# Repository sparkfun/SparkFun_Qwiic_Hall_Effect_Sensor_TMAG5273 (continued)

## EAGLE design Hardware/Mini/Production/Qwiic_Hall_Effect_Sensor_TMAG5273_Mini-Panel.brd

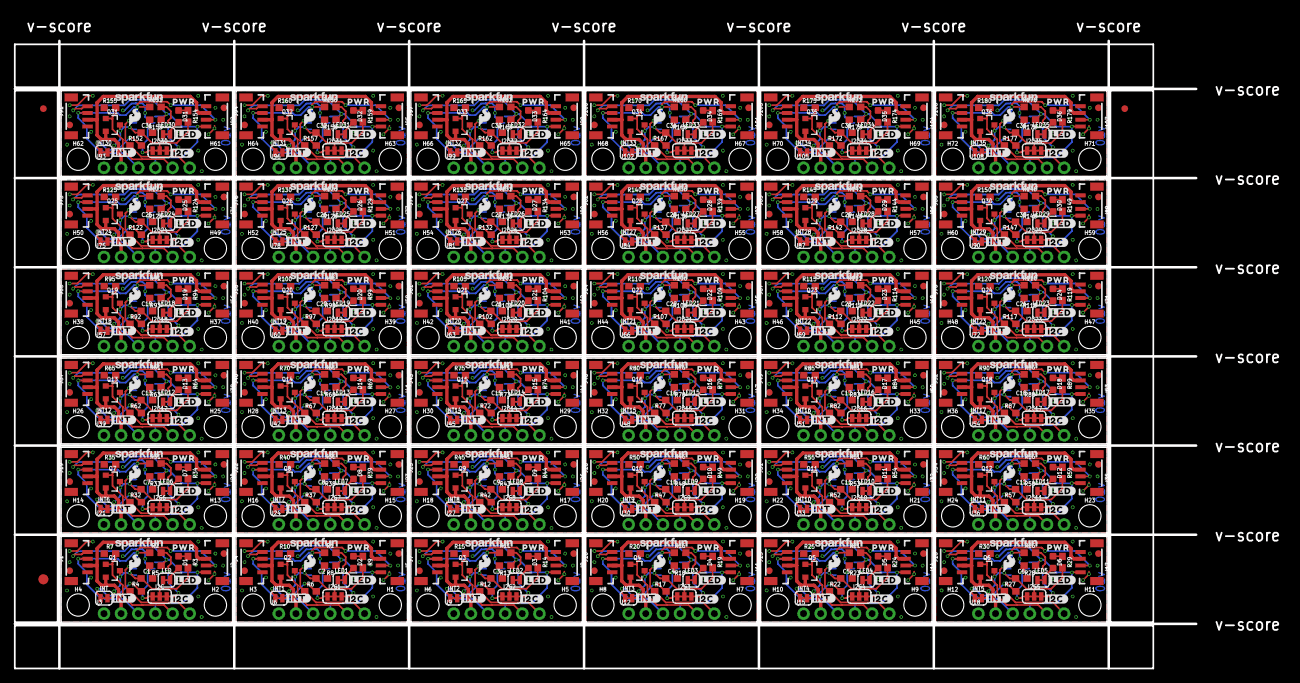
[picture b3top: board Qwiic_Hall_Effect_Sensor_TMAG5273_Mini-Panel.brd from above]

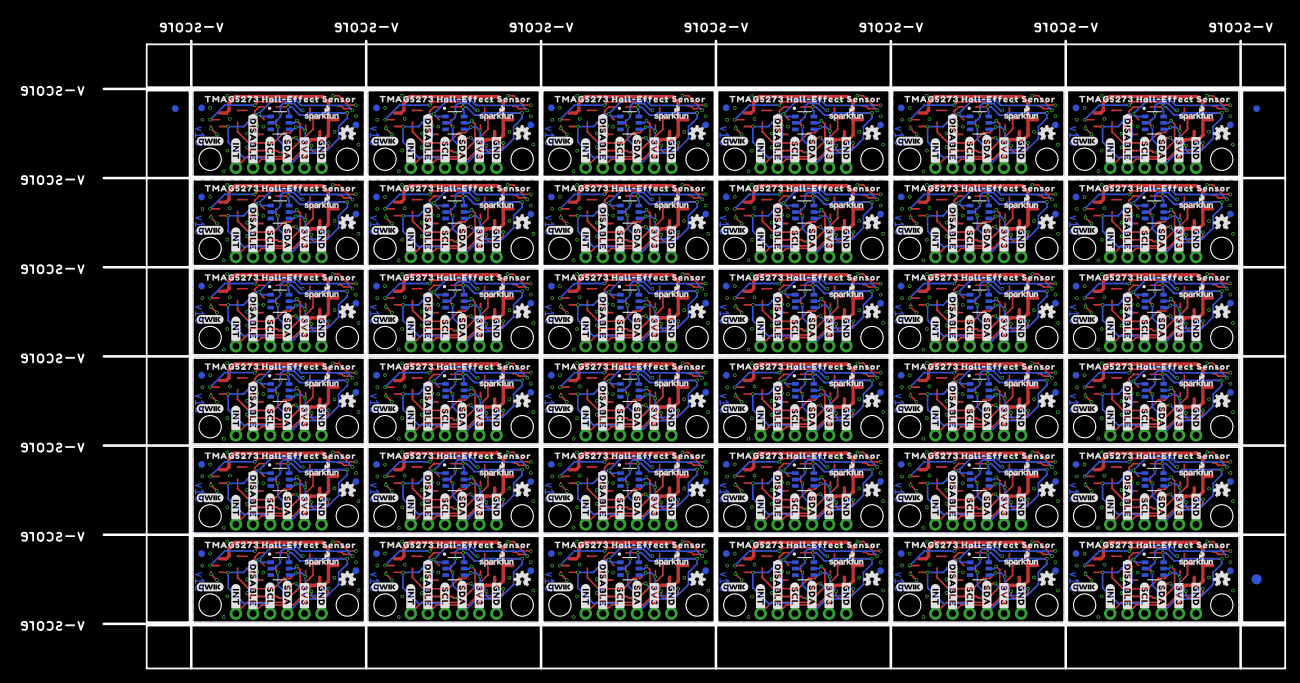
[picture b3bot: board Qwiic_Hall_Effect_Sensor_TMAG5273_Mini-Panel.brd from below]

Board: 2 copper layers, 188.2 x 96.8 mm, 1338 parts (471 on the bottom side), 432 nets.

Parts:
C1, C2, C3, C4, C5, C6, C7, C8, C9, C10, C11, C12, C13, C14, C15, C16, C17, C18, C19, C20, C21, C22, C23, C24, C25, C26, C27, C28, C29, C30, C31, C32, C33, C34, C35, C36: 0.1uF; 0603
D1, D2, D3, D4, D5, D6, D7, D8, D9, D10, D11, D12, D13, D14, D15, D16, D17, D18, D19, D20, D21, D22, D23, D24, D25, D26, D27, D28, D29, D30, D31, D32, D33, D34, D35, D36: Red; LED-0603
E$1, E$2, E$3, E$4: FIDUCIAL-1X2
E$5, E$6: FIDUCIAL-1.5X3
FD1, FD2, FD3, FD4, FD5, FD6, FD7, FD8, FD9, FD10, FD11, FD12, FD13, FD14, FD15, FD16, FD17, FD18, FD19, FD20, FD21, FD22, FD23, FD24, FD25, FD26, FD27, FD28, FD29, FD30, FD31, FD32, FD33, FD34, FD35, FD36, FD37, FD38, FD39, FD40, FD41, FD42, FD43, FD44, FD45, FD46, FD47, FD48, FD49, FD50, FD51, FD52, FD53, FD54, FD55, FD56, FD57, FD58, FD59, FD60, FD61, FD62, FD63, FD64, FD65, FD66, FD67, FD68, FD69, FD70, FD71, FD72, FD73, FD74, FD75, FD76, FD77, FD78, FD79, FD80, FD81, FD82, FD83, FD84, FD85, FD86, FD87, FD88, FD89, FD90, FD91, FD92, FD93, FD94, FD95, FD96, FD97, FD98, FD99, FD100, FD101, FD102, FD103, FD104, FD105, FD106, FD107, FD108, FD109, FD110, FD111, FD112, FD113, FD114, FD115, FD116, FD117, FD118, FD119, FD120, FD121, FD122, FD123, FD124, FD125, FD126, FD127, FD128, FD129, FD130, FD131, FD132, FD133, FD134, FD135, FD136, FD137, FD138, FD139, FD140, FD141, FD142, FD143, FD144: FIDUCIAL1X2; FIDUCIAL-1X2
H1, H2, H3, H4, H5, H6, H7, H8, H9, H10, H11, H12, H13, H14, H15, H16, H17, H18, H19, H20, H21, H22, H23, H24, H25, H26, H27, H28, H29, H30, H31, H32, H33, H34, H35, H36, H37, H38, H39, H40, H41, H42, H43, H44, H45, H46, H47, H48, H49, H50, H51, H52, H53, H54, H55, H56, H57, H58, H59, H60, H61, H62, H63, H64, H65, H66, H67, H68, H69, H70, H71, H72: STAND-OFF
I2C, I2C1, I2C2, I2C3, I2C4, I2C5, I2C6, I2C7, I2C8, I2C9, I2C10, I2C11, I2C12, I2C13, I2C14, I2C15, I2C16, I2C17, I2C18, I2C19, I2C20, I2C21, I2C22, I2C23, I2C24, I2C25, I2C26, I2C27, I2C28, I2C29, I2C30, I2C31, I2C32, I2C33, I2C34, I2C35: JUMPER-SMT_3_2-NC_TRACE_SILK; SMT-JUMPER_3_2-NC_TRACE_SILK
INT, INT1, INT2, INT3, INT4, INT5, INT6, INT7, INT8, INT9, INT10, INT11, INT12, INT13, INT14, INT15, INT16, INT17, INT18, INT19, INT20, INT21, INT22, INT23, INT24, INT25, INT26, INT27, INT28, INT29, INT30, INT31, INT32, INT33, INT34, INT35: JUMPER-SMT_2_NC_TRACE_SILK; SMT-JUMPER_2_NC_TRACE_SILK
J1, J2, J4, J5, J7, J8, J10, J11, J13, J14, J16, J17, J19, J20, J22, J23, J25, J26, J28, J29, J31, J32, J34, J35, J37, J38, J40, J41, J43, J44, J46, J47, J49, J50, J52, J53, J55, J56, J58, J59, J61, J62, J64, J65, J67, J68, J70, J71, J73, J74, J76, J77, J79, J80, J82, J83, J85, J86, J88, J89, J91, J92, J94, J95, J97, J98, J100, J101, J103, J104, J106, J107: Vertical Qwiic Connector; JST04_1MM_VERT
J3, J6, J9, J12, J15, J18, J21, J24, J27, J30, J33, J36, J39, J42, J45, J48, J51, J54, J57, J60, J63, J66, J69, J72, J75, J78, J81, J84, J87, J90, J93, J96, J99, J102, J105, J108: 1X06_NO_SILK
LED, LED1, LED2, LED3, LED4, LED5, LED6, LED7, LED8, LED9, LED10, LED11, LED12, LED13, LED14, LED15, LED16, LED17, LED18, LED19, LED20, LED21, LED22, LED23, LED24, LED25, LED26, LED27, LED28, LED29, LED30, LED31, LED32, LED33, LED34, LED35: JUMPER-SMT_2_NC_TRACE_SILK; SMT-JUMPER_2_NC_TRACE_SILK
LOGO1, LOGO5, LOGO11, LOGO16, LOGO21, LOGO26, LOGO31, LOGO36, LOGO41, LOGO46, LOGO51, LOGO56, LOGO61, LOGO66, LOGO71, LOGO76, LOGO81, LOGO86, LOGO91, LOGO96, LOGO101, LOGO106, LOGO111, LOGO116, LOGO121, LOGO126, LOGO131, LOGO136, LOGO141, LOGO146, LOGO151, LOGO156, LOGO161, LOGO166, LOGO171, LOGO176: OSHW-LOGOMINI; OSHW-LOGO-MINI
LOGO2, LOGO7, LOGO12, LOGO17, LOGO22, LOGO27, LOGO32, LOGO37, LOGO42, LOGO47, LOGO52, LOGO57, LOGO62, LOGO67, LOGO72, LOGO77, LOGO82, LOGO87, LOGO92, LOGO97, LOGO102, LOGO107, LOGO112, LOGO117, LOGO122, LOGO127, LOGO132, LOGO137, LOGO142, LOGO147, LOGO152, LOGO157, LOGO162, LOGO167, LOGO172, LOGO177: SFE_LOGO_NAME_FLAME5_MM; SFE_LOGO_NAME_FLAME_5MM
LOGO3, LOGO8, LOGO13, LOGO18, LOGO23, LOGO28, LOGO33, LOGO38, LOGO43, LOGO48, LOGO53, LOGO58, LOGO63, LOGO68, LOGO73, LOGO78, LOGO83, LOGO88, LOGO93, LOGO98, LOGO103, LOGO108, LOGO113, LOGO118, LOGO123, LOGO128, LOGO133, LOGO138, LOGO143, LOGO148, LOGO153, LOGO158, LOGO163, LOGO168, LOGO173, LOGO178: QWIIC_LOGO_4MM; QWIIC_4MM
LOGO4, LOGO9, LOGO14, LOGO19, LOGO24, LOGO29, LOGO34, LOGO39, LOGO44, LOGO49, LOGO54, LOGO59, LOGO64, LOGO69, LOGO74, LOGO79, LOGO84, LOGO89, LOGO94, LOGO99, LOGO104, LOGO109, LOGO114, LOGO119, LOGO124, LOGO129, LOGO134, LOGO139, LOGO144, LOGO149, LOGO154, LOGO159, LOGO164, LOGO169, LOGO174, LOGO179: SFE_LOGO_NAME7_MM; SFE_LOGO_NAME_7MM
LOGO6, LOGO10, LOGO15, LOGO20, LOGO25, LOGO30, LOGO35, LOGO40, LOGO45, LOGO50, LOGO55, LOGO60, LOGO65, LOGO70, LOGO75, LOGO80, LOGO85, LOGO90, LOGO95, LOGO100, LOGO105, LOGO110, LOGO115, LOGO120, LOGO125, LOGO130, LOGO135, LOGO140, LOGO145, LOGO150, LOGO155, LOGO160, LOGO165, LOGO170, LOGO175, LOGO180: SFE_LOGO_FLAME.1_INCH; SFE_LOGO_FLAME_.1
Q1, Q2, Q3, Q4, Q5, Q6, Q7, Q8, Q9, Q10, Q11, Q12, Q13, Q14, Q15, Q16, Q17, Q18, Q19, Q20, Q21, Q22, Q23, Q24, Q25, Q26, Q27, Q28, Q29, Q30, Q31, Q32, Q33, Q34, Q35, Q36: 20V/4.2A/52mΩ/1.4W; SOT23-3
R1, R2, R5, R8, R11, R13, R16, R18, R21, R23, R26, R28, R31, R33, R36, R38, R41, R43, R46, R48, R51, R53, R56, R58, R61, R63, R66, R68, R71, R73, R76, R78, R81, R83, R86, R88, R91, R93, R96, R98, R101, R103, R106, R108, R111, R113, R116, R118, R121, R123, R126, R128, R131, R133, R136, R138, R141, R143, R146, R148, R151, R153, R156, R158, R161, R163, R166, R168, R171, R173, R176, R178: 2.2k; 0603
R3, R9, R14, R19, R24, R29, R34, R39, R44, R49, R54, R59, R64, R69, R74, R79, R84, R89, R94, R99, R104, R109, R114, R119, R124, R129, R134, R139, R144, R149, R154, R159, R164, R169, R174, R179: 4.7k; 0603
R4, R6, R7, R10, R12, R15, R17, R20, R22, R25, R27, R30, R32, R35, R37, R40, R42, R45, R47, R50, R52, R55, R57, R60, R62, R65, R67, R70, R72, R75, R77, R80, R82, R85, R87, R90, R92, R95, R97, R100, R102, R105, R107, R110, R112, R115, R117, R120, R122, R125, R127, R130, R132, R135, R137, R140, R142, R145, R147, R150, R152, R155, R157, R160, R162, R165, R167, R170, R172, R175, R177, R180: 10k; 0603
U1, U2, U3, U4, U5, U6, U7, U8, U9, U10, U11, U12, U13, U14, U15, U16, U17, U18, U19, U20, U21, U22, U23, U24, U25, U26, U27, U28, U29, U30, U31, U32, U33, U34, U35, U36: TMAG5273; SOT23-6_DBV_TEX
U$1, U$19, U$30, U$41, U$52, U$63, U$74, U$85, U$96, U$107, U$118, U$129, U$140, U$151, U$162, U$173, U$184, U$195, U$206, U$217, U$228, U$239, U$250, U$261, U$272, U$283, U$294, U$305, U$316, U$327, U$338, U$349, U$360, U$371, U$382, U$393: PWR5282
U$2, U$11, U$23, U$34, U$45, U$56, U$67, U$78, U$89, U$100, U$111, U$122, U$133, U$144, U$155, U$166, U$177, U$188, U$199, U$210, U$221, U$232, U$243, U$254, U$265, U$276, U$287, U$298, U$309, U$320, U$331, U$342, U$353, U$364, U$375, U$386: #SCL#38
U$3, U$13, U$24, U$35, U$46, U$57, U$68, U$79, U$90, U$101, U$112, U$123, U$134, U$145, U$156, U$167, U$178, U$189, U$200, U$211, U$222, U$233, U$244, U$255, U$266, U$277, U$288, U$299, U$310, U$321, U$332, U$343, U$354, U$365, U$376, U$387: #SDA#37
U$4, U$14, U$25, U$36, U$47, U$58, U$69, U$80, U$91, U$102, U$113, U$124, U$135, U$146, U$157, U$168, U$179, U$190, U$201, U$212, U$223, U$234, U$245, U$256, U$267, U$278, U$289, U$300, U$311, U$322, U$333, U$344, U$355, U$366, U$377, U$388: #3V3#37
U$5, U$15, U$26, U$37, U$48, U$59, U$70, U$81, U$92, U$103, U$114, U$125, U$136, U$147, U$158, U$169, U$180, U$191, U$202, U$213, U$224, U$235, U$246, U$257, U$268, U$279, U$290, U$301, U$312, U$323, U$334, U$345, U$356, U$367, U$378, U$389: #GND#36
U$6, U$16, U$27, U$38, U$49, U$60, U$71, U$82, U$93, U$104, U$115, U$126, U$137, U$148, U$159, U$170, U$181, U$192, U$203, U$214, U$225, U$236, U$247, U$258, U$269, U$280, U$291, U$302, U$313, U$324, U$335, U$346, U$357, U$368, U$379, U$390: TMAG5273_HALL#EFFECT_SENSOR0
U$7, U$22, U$33, U$44, U$55, U$66, U$77, U$88, U$99, U$110, U$121, U$132, U$143, U$154, U$165, U$176, U$187, U$198, U$209, U$220, U$231, U$242, U$253, U$264, U$275, U$286, U$297, U$308, U$319, U$330, U$341, U$352, U$363, U$374, U$385, U$396: #DISABLE#5291
U$8, U$17, U$28, U$39, U$50, U$61, U$72, U$83, U$94, U$105, U$116, U$127, U$138, U$149, U$160, U$171, U$182, U$193, U$204, U$215, U$226, U$237, U$248, U$259, U$270, U$281, U$292, U$303, U$314, U$325, U$336, U$347, U$358, U$369, U$380, U$391: #I2C#5276
U$9, U$20, U$31, U$42, U$53, U$64, U$75, U$86, U$97, U$108, U$119, U$130, U$141, U$152, U$163, U$174, U$185, U$196, U$207, U$218, U$229, U$240, U$251, U$262, U$273, U$284, U$295, U$306, U$317, U$328, U$339, U$350, U$361, U$372, U$383, U$394: #INT#5285
U$10, U$18, U$29, U$40, U$51, U$62, U$73, U$84, U$95, U$106, U$117, U$128, U$139, U$150, U$161, U$172, U$183, U$194, U$205, U$216, U$227, U$238, U$249, U$260, U$271, U$282, U$293, U$304, U$315, U$326, U$337, U$348, U$359, U$370, U$381, U$392: #LED#5275
U$12, U$21, U$32, U$43, U$54, U$65, U$76, U$87, U$98, U$109, U$120, U$131, U$142, U$153, U$164, U$175, U$186, U$197, U$208, U$219, U$230, U$241, U$252, U$263, U$274, U$285, U$296, U$307, U$318, U$329, U$340, U$351, U$362, U$373, U$384, U$395: #INT#5287

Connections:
3.3V: J1.2, J2.2, J3.2, Q1.2
3.3V1: J4.2, J5.2, J6.2, Q2.2
3.3V2: J7.2, J8.2, J9.2, Q3.2
3.3V3: J10.2, J11.2, J12.2, Q4.2
3.3V4: J13.2, J14.2, J15.2, Q5.2
3.3V5: J16.2, J17.2, J18.2, Q6.2
3.3V6: J19.2, J20.2, J21.2, Q7.2
3.3V7: J22.2, J23.2, J24.2, Q8.2
3.3V8: J25.2, J26.2, J27.2, Q9.2
3.3V9: J28.2, J29.2, J30.2, Q10.2
3.3V10: J31.2, J32.2, J33.2, Q11.2
3.3V11: J34.2, J35.2, J36.2, Q12.2
3.3V12: J37.2, J38.2, J39.2, Q13.2
3.3V13: J40.2, J41.2, J42.2, Q14.2
3.3V14: J43.2, J44.2, J45.2, Q15.2
3.3V15: J46.2, J47.2, J48.2, Q16.2
3.3V16: J49.2, J50.2, J51.2, Q17.2
3.3V17: J52.2, J53.2, J54.2, Q18.2
3.3V18: J55.2, J56.2, J57.2, Q19.2
3.3V19: J58.2, J59.2, J60.2, Q20.2
3.3V20: J61.2, J62.2, J63.2, Q21.2
3.3V21: J64.2, J65.2, J66.2, Q22.2
3.3V22: J67.2, J68.2, J69.2, Q23.2
3.3V23: J70.2, J71.2, J72.2, Q24.2
3.3V24: J73.2, J74.2, J75.2, Q25.2
3.3V25: J76.2, J77.2, J78.2, Q26.2
3.3V26: J79.2, J80.2, J81.2, Q27.2
3.3V27: J82.2, J83.2, J84.2, Q28.2
3.3V28: J85.2, J86.2, J87.2, Q29.2
3.3V29: J88.2, J89.2, J90.2, Q30.2
3.3V30: J91.2, J92.2, J93.2, Q31.2
3.3V31: J94.2, J95.2, J96.2, Q32.2
3.3V32: J97.2, J98.2, J99.2, Q33.2
3.3V33: J100.2, J101.2, J102.2, Q34.2
3.3V34: J103.2, J104.2, J105.2, Q35.2
3.3V35: J106.2, J107.2, J108.2, Q36.2
3.3V_SW: C1.1, I2C.2, INT.2, Q1.3, R3.2, U1.4
3.3V_SW1: C2.1, I2C1.2, INT1.2, Q2.3, R9.2, U2.4
3.3V_SW2: C3.1, I2C2.2, INT2.2, Q3.3, R14.2, U3.4
3.3V_SW3: C4.1, I2C3.2, INT3.2, Q4.3, R19.2, U4.4
3.3V_SW4: C5.1, I2C4.2, INT4.2, Q5.3, R24.2, U5.4
3.3V_SW5: C6.1, I2C5.2, INT5.2, Q6.3, R29.2, U6.4
3.3V_SW6: C7.1, I2C6.2, INT6.2, Q7.3, R34.2, U7.4
3.3V_SW7: C8.1, I2C7.2, INT7.2, Q8.3, R39.2, U8.4
3.3V_SW8: C9.1, I2C8.2, INT8.2, Q9.3, R44.2, U9.4
3.3V_SW9: C10.1, I2C9.2, INT9.2, Q10.3, R49.2, U10.4
3.3V_SW10: C11.1, I2C10.2, INT10.2, Q11.3, R54.2, U11.4
3.3V_SW11: C12.1, I2C11.2, INT11.2, Q12.3, R59.2, U12.4
3.3V_SW12: C13.1, I2C12.2, INT12.2, Q13.3, R64.2, U13.4
3.3V_SW13: C14.1, I2C13.2, INT13.2, Q14.3, R69.2, U14.4
3.3V_SW14: C15.1, I2C14.2, INT14.2, Q15.3, R74.2, U15.4
3.3V_SW15: C16.1, I2C15.2, INT15.2, Q16.3, R79.2, U16.4
3.3V_SW16: C17.1, I2C16.2, INT16.2, Q17.3, R84.2, U17.4
3.3V_SW17: C18.1, I2C17.2, INT17.2, Q18.3, R89.2, U18.4
3.3V_SW18: C19.1, I2C18.2, INT18.2, Q19.3, R94.2, U19.4
3.3V_SW19: C20.1, I2C19.2, INT19.2, Q20.3, R99.2, U20.4
3.3V_SW20: C21.1, I2C20.2, INT20.2, Q21.3, R104.2, U21.4
3.3V_SW21: C22.1, I2C21.2, INT21.2, Q22.3, R109.2, U22.4
3.3V_SW22: C23.1, I2C22.2, INT22.2, Q23.3, R114.2, U23.4
3.3V_SW23: C24.1, I2C23.2, INT23.2, Q24.3, R119.2, U24.4
3.3V_SW24: C25.1, I2C24.2, INT24.2, Q25.3, R124.2, U25.4
3.3V_SW25: C26.1, I2C25.2, INT25.2, Q26.3, R129.2, U26.4
3.3V_SW26: C27.1, I2C26.2, INT26.2, Q27.3, R134.2, U27.4
3.3V_SW27: C28.1, I2C27.2, INT27.2, Q28.3, R139.2, U28.4
3.3V_SW28: C29.1, I2C28.2, INT28.2, Q29.3, R144.2, U29.4
3.3V_SW29: C30.1, I2C29.2, INT29.2, Q30.3, R149.2, U30.4
3.3V_SW30: C31.1, I2C30.2, INT30.2, Q31.3, R154.2, U31.4
3.3V_SW31: C32.1, I2C31.2, INT31.2, Q32.3, R159.2, U32.4
3.3V_SW32: C33.1, I2C32.2, INT32.2, Q33.3, R164.2, U33.4
3.3V_SW33: C34.1, I2C33.2, INT33.2, Q34.3, R169.2, U34.4
3.3V_SW34: C35.1, I2C34.2, INT34.2, Q35.3, R174.2, U35.4
3.3V_SW35: C36.1, I2C35.2, INT35.2, Q36.3, R179.2, U36.4
!INT: J3.6, R4.1, U1.5
!INT1: J6.6, R6.1, U2.5
!INT2: J9.6, R12.1, U3.5
!INT3: J12.6, R17.1, U4.5
!INT4: J15.6, R22.1, U5.5
!INT5: J18.6, R27.1, U6.5
!INT6: J21.6, R32.1, U7.5
!INT7: J24.6, R37.1, U8.5
!INT8: J27.6, R42.1, U9.5
!INT9: J30.6, R47.1, U10.5
!INT10: J33.6, R52.1, U11.5
!INT11: J36.6, R57.1, U12.5
!INT12: J39.6, R62.1, U13.5
!INT13: J42.6, R67.1, U14.5
!INT14: J45.6, R72.1, U15.5
!INT15: J48.6, R77.1, U16.5
!INT16: J51.6, R82.1, U17.5
!INT17: J54.6, R87.1, U18.5
!INT18: J57.6, R92.1, U19.5
!INT19: J60.6, R97.1, U20.5
!INT20: J63.6, R102.1, U21.5
!INT21: J66.6, R107.1, U22.5
!INT22: J69.6, R112.1, U23.5
!INT23: J72.6, R117.1, U24.5
!INT24: J75.6, R122.1, U25.5
!INT25: J78.6, R127.1, U26.5
!INT26: J81.6, R132.1, U27.5
!INT27: J84.6, R137.1, U28.5
!INT28: J87.6, R142.1, U29.5
!INT29: J90.6, R147.1, U30.5
!INT30: J93.6, R152.1, U31.5
!INT31: J96.6, R157.1, U32.5
!INT32: J99.6, R162.1, U33.5
!INT33: J102.6, R167.1, U34.5
!INT34: J105.6, R172.1, U35.5
!INT35: J108.6, R177.1, U36.5
DISABLE: J3.5, Q1.1, R7.2
DISABLE1: J6.5, Q2.1, R10.2
DISABLE2: J9.5, Q3.1, R15.2
DISABLE3: J12.5, Q4.1, R20.2
DISABLE4: J15.5, Q5.1, R25.2
DISABLE5: J18.5, Q6.1, R30.2
DISABLE6: J21.5, Q7.1, R35.2
DISABLE7: J24.5, Q8.1, R40.2
DISABLE8: J27.5, Q9.1, R45.2
DISABLE9: J30.5, Q10.1, R50.2
DISABLE10: J33.5, Q11.1, R55.2
DISABLE11: J36.5, Q12.1, R60.2
DISABLE12: J39.5, Q13.1, R65.2
DISABLE13: J42.5, Q14.1, R70.2
DISABLE14: J45.5, Q15.1, R75.2
DISABLE15: J48.5, Q16.1, R80.2
DISABLE16: J51.5, Q17.1, R85.2
DISABLE17: J54.5, Q18.1, R90.2
DISABLE18: J57.5, Q19.1, R95.2
DISABLE19: J60.5, Q20.1, R100.2
DISABLE20: J63.5, Q21.1, R105.2
DISABLE21: J66.5, Q22.1, R110.2
DISABLE22: J69.5, Q23.1, R115.2
DISABLE23: J72.5, Q24.1, R120.2
DISABLE24: J75.5, Q25.1, R125.2
DISABLE25: J78.5, Q26.1, R130.2
DISABLE26: J81.5, Q27.1, R135.2
DISABLE27: J84.5, Q28.1, R140.2
DISABLE28: J87.5, Q29.1, R145.2
DISABLE29: J90.5, Q30.1, R150.2
DISABLE30: J93.5, Q31.1, R155.2
DISABLE31: J96.5, Q32.1, R160.2
DISABLE32: J99.5, Q33.1, R165.2
DISABLE33: J102.5, Q34.1, R170.2
DISABLE34: J105.5, Q35.1, R175.2
DISABLE35: J108.5, Q36.1, R180.2
GND: C1.2, J1.1, J2.1, J3.1, LED.1, R7.1, U1.2, U1.3
GND1: C2.2, J4.1, J5.1, J6.1, LED1.1, R10.1, U2.2, U2.3
GND2: C3.2, J7.1, J8.1, J9.1, LED2.1, R15.1, U3.2, U3.3
GND3: C4.2, J10.1, J11.1, J12.1, LED3.1, R20.1, U4.2, U4.3
GND4: C5.2, J13.1, J14.1, J15.1, LED4.1, R25.1, U5.2, U5.3
GND5: C6.2, J16.1, J17.1, J18.1, LED5.1, R30.1, U6.2, U6.3
GND6: C7.2, J19.1, J20.1, J21.1, LED6.1, R35.1, U7.2, U7.3
GND7: C8.2, J22.1, J23.1, J24.1, LED7.1, R40.1, U8.2, U8.3
GND8: C9.2, J25.1, J26.1, J27.1, LED8.1, R45.1, U9.2, U9.3
GND9: C10.2, J28.1, J29.1, J30.1, LED9.1, R50.1, U10.2, U10.3
GND10: C11.2, J31.1, J32.1, J33.1, LED10.1, R55.1, U11.2, U11.3
GND11: C12.2, J34.1, J35.1, J36.1, LED11.1, R60.1, U12.2, U12.3
GND12: C13.2, J37.1, J38.1, J39.1, LED12.1, R65.1, U13.2, U13.3
GND13: C14.2, J40.1, J41.1, J42.1, LED13.1, R70.1, U14.2, U14.3
GND14: C15.2, J43.1, J44.1, J45.1, LED14.1, R75.1, U15.2, U15.3
GND15: C16.2, J46.1, J47.1, J48.1, LED15.1, R80.1, U16.2, U16.3
GND16: C17.2, J49.1, J50.1, J51.1, LED16.1, R85.1, U17.2, U17.3
GND17: C18.2, J52.1, J53.1, J54.1, LED17.1, R90.1, U18.2, U18.3
GND18: C19.2, J55.1, J56.1, J57.1, LED18.1, R95.1, U19.2, U19.3
GND19: C20.2, J58.1, J59.1, J60.1, LED19.1, R100.1, U20.2, U20.3
GND20: C21.2, J61.1, J62.1, J63.1, LED20.1, R105.1, U21.2, U21.3
GND21: C22.2, J64.1, J65.1, J66.1, LED21.1, R110.1, U22.2, U22.3
GND22: C23.2, J67.1, J68.1, J69.1, LED22.1, R115.1, U23.2, U23.3
GND23: C24.2, J70.1, J71.1, J72.1, LED23.1, R120.1, U24.2, U24.3
GND24: C25.2, J73.1, J74.1, J75.1, LED24.1, R125.1, U25.2, U25.3
GND25: C26.2, J76.1, J77.1, J78.1, LED25.1, R130.1, U26.2, U26.3
GND26: C27.2, J79.1, J80.1, J81.1, LED26.1, R135.1, U27.2, U27.3
GND27: C28.2, J82.1, J83.1, J84.1, LED27.1, R140.1, U28.2, U28.3
GND28: C29.2, J85.1, J86.1, J87.1, LED28.1, R145.1, U29.2, U29.3
GND29: C30.2, J88.1, J89.1, J90.1, LED29.1, R150.1, U30.2, U30.3
GND30: C31.2, J91.1, J92.1, J93.1, LED30.1, R155.1, U31.2, U31.3
GND31: C32.2, J94.1, J95.1, J96.1, LED31.1, R160.1, U32.2, U32.3
GND32: C33.2, J97.1, J98.1, J99.1, LED32.1, R165.1, U33.2, U33.3
GND33: C34.2, J100.1, J101.1, J102.1, LED33.1, R170.1, U34.2, U34.3
GND34: C35.2, J103.1, J104.1, J105.1, LED34.1, R175.1, U35.2, U35.3
GND35: C36.2, J106.1, J107.1, J108.1, LED35.1, R180.1, U36.2, U36.3
unnamed: D1.C, LED.2
unnamed: I2C.3, R2.2
unnamed: D2.A, R9.1
unnamed: D1.A, R3.1
unnamed: INT.1, R4.2
unnamed: I2C.1, R5.2
unnamed: D2.C, LED1.2
unnamed: INT1.1, R6.2
unnamed: I2C1.3, R1.2
unnamed: I2C1.1, R8.2
unnamed: D3.A, R14.1
unnamed: D3.C, LED2.2
unnamed: INT2.1, R12.2
unnamed: I2C2.3, R11.2
unnamed: I2C2.1, R13.2
unnamed: D4.A, R19.1
unnamed: D4.C, LED3.2
unnamed: INT3.1, R17.2
unnamed: I2C3.3, R16.2
unnamed: I2C3.1, R18.2
unnamed: D5.A, R24.1
unnamed: D5.C, LED4.2
unnamed: INT4.1, R22.2
unnamed: I2C4.3, R21.2
unnamed: I2C4.1, R23.2
unnamed: D6.A, R29.1
unnamed: D6.C, LED5.2
unnamed: INT5.1, R27.2
unnamed: I2C5.3, R26.2
unnamed: I2C5.1, R28.2
unnamed: D7.A, R34.1
unnamed: D7.C, LED6.2
unnamed: INT6.1, R32.2
unnamed: I2C6.3, R31.2
unnamed: I2C6.1, R33.2
unnamed: D8.A, R39.1
unnamed: D8.C, LED7.2
unnamed: INT7.1, R37.2
unnamed: I2C7.3, R36.2
unnamed: I2C7.1, R38.2
unnamed: D9.A, R44.1
unnamed: D9.C, LED8.2
unnamed: INT8.1, R42.2
unnamed: I2C8.3, R41.2
unnamed: I2C8.1, R43.2
unnamed: D10.A, R49.1
unnamed: D10.C, LED9.2
unnamed: INT9.1, R47.2
unnamed: I2C9.3, R46.2
unnamed: I2C9.1, R48.2
unnamed: D11.A, R54.1
unnamed: D11.C, LED10.2
unnamed: INT10.1, R52.2
unnamed: I2C10.3, R51.2
unnamed: I2C10.1, R53.2
unnamed: D12.A, R59.1
unnamed: D12.C, LED11.2
unnamed: INT11.1, R57.2
unnamed: I2C11.3, R56.2
unnamed: I2C11.1, R58.2
unnamed: D13.A, R64.1
unnamed: D13.C, LED12.2
unnamed: INT12.1, R62.2
unnamed: I2C12.3, R61.2
unnamed: I2C12.1, R63.2
unnamed: D14.A, R69.1
unnamed: D14.C, LED13.2
unnamed: INT13.1, R67.2
unnamed: I2C13.3, R66.2
unnamed: I2C13.1, R68.2
unnamed: D15.A, R74.1
unnamed: D15.C, LED14.2
unnamed: INT14.1, R72.2
unnamed: I2C14.3, R71.2
unnamed: I2C14.1, R73.2
unnamed: D16.A, R79.1
unnamed: D16.C, LED15.2
unnamed: INT15.1, R77.2
unnamed: I2C15.3, R76.2
unnamed: I2C15.1, R78.2
unnamed: D17.A, R84.1
unnamed: D17.C, LED16.2
unnamed: INT16.1, R82.2
unnamed: I2C16.3, R81.2
unnamed: I2C16.1, R83.2
unnamed: D18.A, R89.1
unnamed: D18.C, LED17.2
unnamed: INT17.1, R87.2
unnamed: I2C17.3, R86.2
unnamed: I2C17.1, R88.2
unnamed: D19.A, R94.1
unnamed: D19.C, LED18.2
unnamed: INT18.1, R92.2
unnamed: I2C18.3, R91.2
unnamed: I2C18.1, R93.2
unnamed: D20.A, R99.1
unnamed: D20.C, LED19.2
unnamed: INT19.1, R97.2
unnamed: I2C19.3, R96.2
unnamed: I2C19.1, R98.2
unnamed: D21.A, R104.1
unnamed: D21.C, LED20.2
unnamed: INT20.1, R102.2
unnamed: I2C20.3, R101.2
unnamed: I2C20.1, R103.2
unnamed: D22.A, R109.1
unnamed: D22.C, LED21.2
unnamed: INT21.1, R107.2
unnamed: I2C21.3, R106.2
unnamed: I2C21.1, R108.2
unnamed: D23.A, R114.1
unnamed: D23.C, LED22.2
unnamed: INT22.1, R112.2
unnamed: I2C22.3, R111.2
unnamed: I2C22.1, R113.2
unnamed: D24.A, R119.1
unnamed: D24.C, LED23.2
unnamed: INT23.1, R117.2
unnamed: I2C23.3, R116.2
unnamed: I2C23.1, R118.2
unnamed: D25.A, R124.1
unnamed: D25.C, LED24.2
unnamed: INT24.1, R122.2
unnamed: I2C24.3, R121.2
unnamed: I2C24.1, R123.2
unnamed: D26.A, R129.1
unnamed: D26.C, LED25.2
unnamed: INT25.1, R127.2
unnamed: I2C25.3, R126.2
unnamed: I2C25.1, R128.2
unnamed: D27.A, R134.1
unnamed: D27.C, LED26.2
unnamed: INT26.1, R132.2
unnamed: I2C26.3, R131.2
unnamed: I2C26.1, R133.2
unnamed: D28.A, R139.1
unnamed: D28.C, LED27.2
unnamed: INT27.1, R137.2
unnamed: I2C27.3, R136.2
unnamed: I2C27.1, R138.2
unnamed: D29.A, R144.1
unnamed: D29.C, LED28.2
unnamed: INT28.1, R142.2
unnamed: I2C28.3, R141.2
unnamed: I2C28.1, R143.2
unnamed: D30.A, R149.1
unnamed: D30.C, LED29.2
unnamed: INT29.1, R147.2
unnamed: I2C29.3, R146.2
unnamed: I2C29.1, R148.2
unnamed: D31.A, R154.1
unnamed: D31.C, LED30.2
unnamed: INT30.1, R152.2
unnamed: I2C30.3, R151.2
unnamed: I2C30.1, R153.2
unnamed: D32.A, R159.1
unnamed: D32.C, LED31.2
unnamed: INT31.1, R157.2
unnamed: I2C31.3, R156.2
unnamed: I2C31.1, R158.2
unnamed: D33.A, R164.1
unnamed: D33.C, LED32.2
unnamed: INT32.1, R162.2
unnamed: I2C32.3, R161.2
unnamed: I2C32.1, R163.2
unnamed: D34.A, R169.1
unnamed: D34.C, LED33.2
unnamed: INT33.1, R167.2
unnamed: I2C33.3, R166.2
unnamed: I2C33.1, R168.2
unnamed: D35.A, R174.1
unnamed: D35.C, LED34.2
unnamed: INT34.1, R172.2
unnamed: I2C34.3, R171.2
unnamed: I2C34.1, R173.2
unnamed: D36.A, R179.1
unnamed: D36.C, LED35.2
unnamed: INT35.1, R177.2
unnamed: I2C35.3, R176.2
unnamed: I2C35.1, R178.2
SCL: J1.4, J2.4, J3.4, R5.1, U1.1
SCL1: J4.4, J5.4, J6.4, R8.1, U2.1
SCL2: J7.4, J8.4, J9.4, R13.1, U3.1
SCL3: J10.4, J11.4, J12.4, R18.1, U4.1
SCL4: J13.4, J14.4, J15.4, R23.1, U5.1
SCL5: J16.4, J17.4, J18.4, R28.1, U6.1
SCL6: J19.4, J20.4, J21.4, R33.1, U7.1
SCL7: J22.4, J23.4, J24.4, R38.1, U8.1
SCL8: J25.4, J26.4, J27.4, R43.1, U9.1
SCL9: J28.4, J29.4, J30.4, R48.1, U10.1
SCL10: J31.4, J32.4, J33.4, R53.1, U11.1
SCL11: J34.4, J35.4, J36.4, R58.1, U12.1
SCL12: J37.4, J38.4, J39.4, R63.1, U13.1
SCL13: J40.4, J41.4, J42.4, R68.1, U14.1
SCL14: J43.4, J44.4, J45.4, R73.1, U15.1
SCL15: J46.4, J47.4, J48.4, R78.1, U16.1
SCL16: J49.4, J50.4, J51.4, R83.1, U17.1
SCL17: J52.4, J53.4, J54.4, R88.1, U18.1
SCL18: J55.4, J56.4, J57.4, R93.1, U19.1
SCL19: J58.4, J59.4, J60.4, R98.1, U20.1
SCL20: J61.4, J62.4, J63.4, R103.1, U21.1
SCL21: J64.4, J65.4, J66.4, R108.1, U22.1
SCL22: J67.4, J68.4, J69.4, R113.1, U23.1
SCL23: J70.4, J71.4, J72.4, R118.1, U24.1
SCL24: J73.4, J74.4, J75.4, R123.1, U25.1
SCL25: J76.4, J77.4, J78.4, R128.1, U26.1
SCL26: J79.4, J80.4, J81.4, R133.1, U27.1
SCL27: J82.4, J83.4, J84.4, R138.1, U28.1
SCL28: J85.4, J86.4, J87.4, R143.1, U29.1
SCL29: J88.4, J89.4, J90.4, R148.1, U30.1
SCL30: J91.4, J92.4, J93.4, R153.1, U31.1
SCL31: J94.4, J95.4, J96.4, R158.1, U32.1
SCL32: J97.4, J98.4, J99.4, R163.1, U33.1
SCL33: J100.4, J101.4, J102.4, R168.1, U34.1
SCL34: J103.4, J104.4, J105.4, R173.1, U35.1
SCL35: J106.4, J107.4, J108.4, R178.1, U36.1
SDA: J1.3, J2.3, J3.3, R2.1, U1.6
SDA1: J4.3, J5.3, J6.3, R1.1, U2.6
SDA2: J7.3, J8.3, J9.3, R11.1, U3.6
SDA3: J10.3, J11.3, J12.3, R16.1, U4.6
SDA4: J13.3, J14.3, J15.3, R21.1, U5.6
SDA5: J16.3, J17.3, J18.3, R26.1, U6.6
SDA6: J19.3, J20.3, J21.3, R31.1, U7.6
SDA7: J22.3, J23.3, J24.3, R36.1, U8.6
SDA8: J25.3, J26.3, J27.3, R41.1, U9.6
SDA9: J28.3, J29.3, J30.3, R46.1, U10.6
SDA10: J31.3, J32.3, J33.3, R51.1, U11.6
SDA11: J34.3, J35.3, J36.3, R56.1, U12.6
SDA12: J37.3, J38.3, J39.3, R61.1, U13.6
SDA13: J40.3, J41.3, J42.3, R66.1, U14.6
SDA14: J43.3, J44.3, J45.3, R71.1, U15.6
SDA15: J46.3, J47.3, J48.3, R76.1, U16.6
SDA16: J49.3, J50.3, J51.3, R81.1, U17.6
SDA17: J52.3, J53.3, J54.3, R86.1, U18.6
SDA18: J55.3, J56.3, J57.3, R91.1, U19.6
SDA19: J58.3, J59.3, J60.3, R96.1, U20.6
SDA20: J61.3, J62.3, J63.3, R101.1, U21.6
SDA21: J64.3, J65.3, J66.3, R106.1, U22.6
SDA22: J67.3, J68.3, J69.3, R111.1, U23.6
SDA23: J70.3, J71.3, J72.3, R116.1, U24.6
SDA24: J73.3, J74.3, J75.3, R121.1, U25.6
SDA25: J76.3, J77.3, J78.3, R126.1, U26.6
SDA26: J79.3, J80.3, J81.3, R131.1, U27.6
SDA27: J82.3, J83.3, J84.3, R136.1, U28.6
SDA28: J85.3, J86.3, J87.3, R141.1, U29.6
SDA29: J88.3, J89.3, J90.3, R146.1, U30.6
SDA30: J91.3, J92.3, J93.3, R151.1, U31.6
SDA31: J94.3, J95.3, J96.3, R156.1, U32.6
SDA32: J97.3, J98.3, J99.3, R161.1, U33.6
SDA33: J100.3, J101.3, J102.3, R166.1, U34.6
SDA34: J103.3, J104.3, J105.3, R171.1, U35.6
SDA35: J106.3, J107.3, J108.3, R176.1, U36.6

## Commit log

2023-09-20 Added datasheet, deleted unneeded folders
    Folder restructure, addition of datasheet, and minimal updates to the README
2023-09-20 Schematic created and TMAG added to library
2023-09-29 Restructured file folders for new board
    Added the micro folder and schematic to the project. Moved the 1x1 board into its own file folder.
2023-10-13 Completed schematic and routing
    Need to finish aesthetics and dimensions to layout. Almost ready for review.
2023-10-13 Updates for design review
    Changed LED and associated resistor to have the correct part and value; added dimension lines and further notes on the layout; adjusted aesthetics in schematic to now be the same as each other (minus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
2023-10-16 Ready for review
    Updates from ENG Checklist - Small tweaks added - updated ordering of PTH headers for SDA and SCL, fixed final errors on design
2023-10-17 Updated !INT silk
    Updated !INT silk to be the correct end (now ( rather than < )
2023-10-17 Design Review Changes
    Adjusted schematic to have the correct power-on reset circuit, along with the change in the layout. The GPIO net was relabled to RESET to match the layout of the board/labeling. Adjusted some labelin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
2023-10-18 Adjusted from design review
    Added truth tables, changed RESET to Disable, adjusted magnetic axis to be centered to the middle of the board, added push button for 1x1 reset option
2023-10-18 Added gerber files
    Files added and now ready for order
2023-10-30 Design review updates
    Addition of gerber files for both mini and 1x1, adjusted board for reds engineering checklist run.
2023-10-31 Updates from design review
    Adjusted traces for better GND connections; changed direction of tail end for the DISABLE pin; changed jumper names in schematic to match layout; added more GND vias to the Mini; updated trace widths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
2023-11-01 Files for ordering
    Re-added the correct panel files for the project along with ordering instructions. Made final adjustments from design review and board is ready for order!
2023-11-27 Updated I2C address in schematic
    Updated the I2C address to the actual address used in the library/for the devices usage
2023-11-28 Add images and logos
    Initial hookup guide images and logos
2023-12-08 Add Technical Documents
    Datasheet, application notes, schematic, board dimensions, etc.
2023-12-08 QR codes
2023-12-08 Update Readme and License
    Updated files
2023-12-08 Add Issue/Contribution Files
2023-12-13 Initial docs commit
2023-12-13 Add deploy workflow
2023-12-13 Update workflow
    The `distutils` module that is utilized by the `mkdocs-monorepo-plugin` has been removed from the latest Python version (3.12). Forcing use of Python 3.11 for compatibility
2023-12-14 Update hookup guide
    Include missing images
    Add warnings for button and magnet
2023-12-14 Move datasheet
    Move folder with datasheets
2023-12-14 Deployed e7cdde6 with MkDocs version: 1.5.3
